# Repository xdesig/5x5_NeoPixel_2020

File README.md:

# Pantalla 25 (5x5) Neopixel 2020

## Aplicación
Con EchidnaBlack

## Serigrafía

## Esquema

Os capacitores son opcionais

## Licencia
Doc. Creative commons. Attribution-ShareAlike 4.0 International (CC BY-SA 4.0) Hard. CERN OHL v.1.2XDeSIG 2036

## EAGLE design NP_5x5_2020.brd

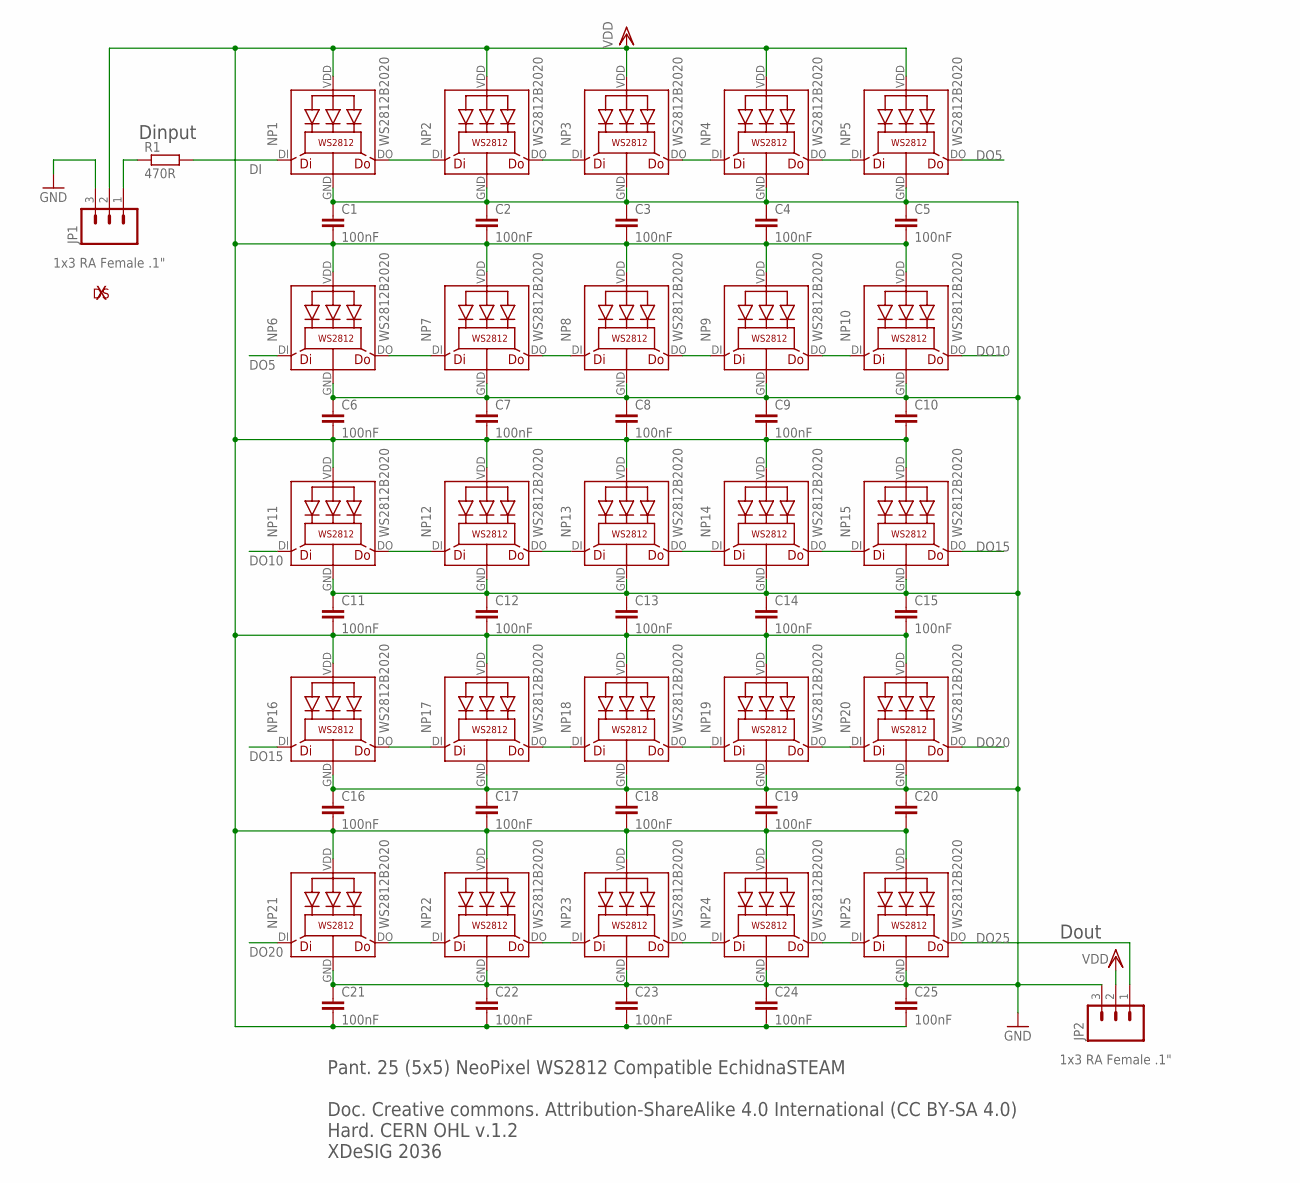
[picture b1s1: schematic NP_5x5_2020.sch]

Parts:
C1, C2, C3, C4, C5, C6, C7, C8, C9, C11, C12, C13, C14, C15, C16, C17, C18, C19, C21, C22, C23, C24, C25: 100nF; C0402
C10, C20: C-EUC0402; C0402
JP1, JP2: 1x3 RA Female .1"; 1X03_SMD_RA_FEMALE
NP1, NP2, NP3, NP4, NP5, NP6, NP7, NP8, NP9, NP10, NP11, NP12, NP13, NP14, NP15, NP16, NP17, NP18, NP19, NP20, NP21, NP22, NP23, NP24, NP25: WS2812B2020; 2020
R1: 470R; R0603
U$1: XDESIG_XDESIG5MM; XDESIG_XDESIG_CU

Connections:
DI: NP1.DI, R1.2
DO5: NP5.DO, NP6.DI
DO10: NP10.DO, NP11.DI
DO15: NP15.DO, NP16.DI
DO20: NP20.DO, NP21.DI
DO25: JP2.1, NP25.DO
GND: C1.1, C2.1, C3.1, C4.1, C5.1, C6.1, C7.1, C8.1, C9.1, C10.1, C11.1, C12.1, C13.1, C14.1, C15.1, C16.1, C17.1, C18.1, C19.1, C20.1, C21.1, C22.1, C23.1, C24.1, C25.1, JP1.3, JP2.3, NP1.GND, NP2.GND, NP3.GND, NP4.GND, NP5.GND, NP6.GND, NP7.GND, NP8.GND, NP9.GND, NP10.GND, NP11.GND, NP12.GND, NP13.GND, NP14.GND, NP15.GND, NP16.GND, NP17.GND, NP18.GND, NP19.GND, NP20.GND, NP21.GND, NP22.GND, NP23.GND, NP24.GND, NP25.GND
unnamed: NP1.DO, NP2.DI
unnamed: NP2.DO, NP3.DI
unnamed: NP3.DO, NP4.DI
unnamed: NP4.DO, NP5.DI
unnamed: NP22.DO, NP23.DI
unnamed: NP23.DO, NP24.DI
unnamed: NP6.DO, NP7.DI
unnamed: NP7.DO, NP8.DI
unnamed: NP8.DO, NP9.DI
unnamed: NP9.DO, NP10.DI
unnamed: NP11.DO, NP12.DI
unnamed: NP12.DO, NP13.DI
unnamed: NP13.DO, NP14.DI
unnamed: NP14.DO, NP15.DI
unnamed: NP16.DO, NP17.DI
unnamed: NP17.DO, NP18.DI
unnamed: NP18.DO, NP19.DI
unnamed: NP19.DO, NP20.DI
unnamed: NP21.DO, NP22.DI
unnamed: NP24.DO, NP25.DI
unnamed: JP1.1, R1.1
VDD: C1.2, C2.2, C3.2, C4.2, C5.2, C6.2, C7.2, C8.2, C9.2, C10.2, C11.2, C12.2, C13.2, C14.2, C15.2, C16.2, C17.2, C18.2, C19.2, C20.2, C21.2, C22.2, C23.2, C24.2, C25.2, JP1.2, JP2.2, NP1.VDD (LEDVDD), NP2.VDD (LEDVDD), NP3.VDD (LEDVDD), NP4.VDD (LEDVDD), NP5.VDD (LEDVDD), NP6.VDD (LEDVDD), NP7.VDD (LEDVDD), NP8.VDD (LEDVDD), NP9.VDD (LEDVDD), NP10.VDD (LEDVDD), NP11.VDD (LEDVDD), NP12.VDD (LEDVDD), NP13.VDD (LEDVDD), NP14.VDD (LEDVDD), NP15.VDD (LEDVDD), NP16.VDD (LEDVDD), NP17.VDD (LEDVDD), NP18.VDD (LEDVDD), NP19.VDD (LEDVDD), NP20.VDD (LEDVDD), NP21.VDD (LEDVDD), NP22.VDD (LEDVDD), NP23.VDD (LEDVDD), NP24.VDD (LEDVDD), NP25.VDD (LEDVDD)

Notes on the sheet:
Dout
Dinput
Pant. 25 (5x5) NeoPixel WS2812 Compatible EchidnaSTEAM Doc. Creative commons. Attribution-ShareAlike 4.0 International (CC BY-SA 4.0) Hard. CERN OHL v.1.2 XDeSIG 2036

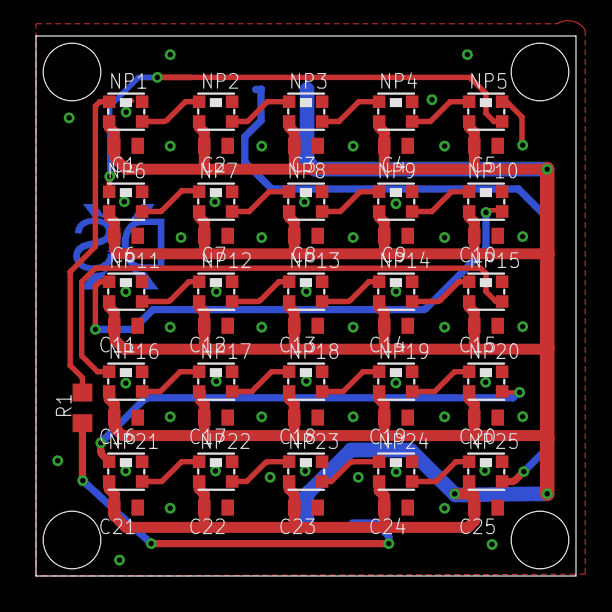
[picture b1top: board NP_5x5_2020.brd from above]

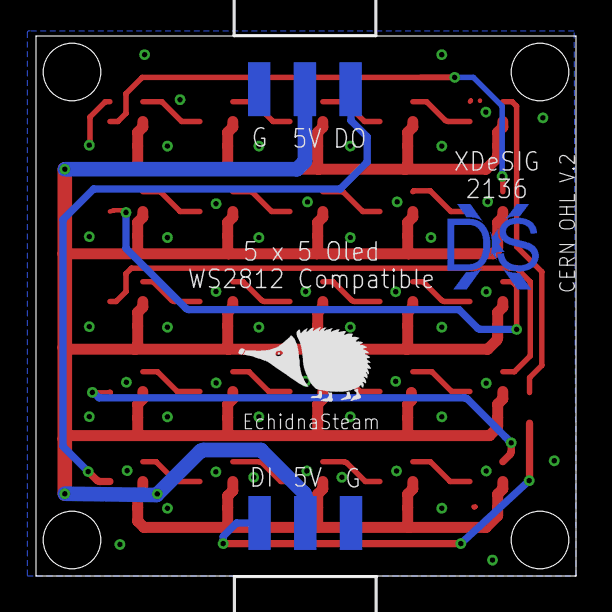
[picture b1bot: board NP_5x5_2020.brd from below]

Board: 2 copper layers, 30.0 x 30.0 mm, 55 parts (4 on the bottom side), 29 nets.

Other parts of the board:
U$3: ECHIDNA_P

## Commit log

2021-09-26 Initial

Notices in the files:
NP_5x5_2020.brd:
CERN OHL V.2
parts and their libraries:
SparkFun-Connectors: Licensing: Creative Commons ShareAlike 4.0 International - https://creativecommons.org/licenses/by-sa/4.0
